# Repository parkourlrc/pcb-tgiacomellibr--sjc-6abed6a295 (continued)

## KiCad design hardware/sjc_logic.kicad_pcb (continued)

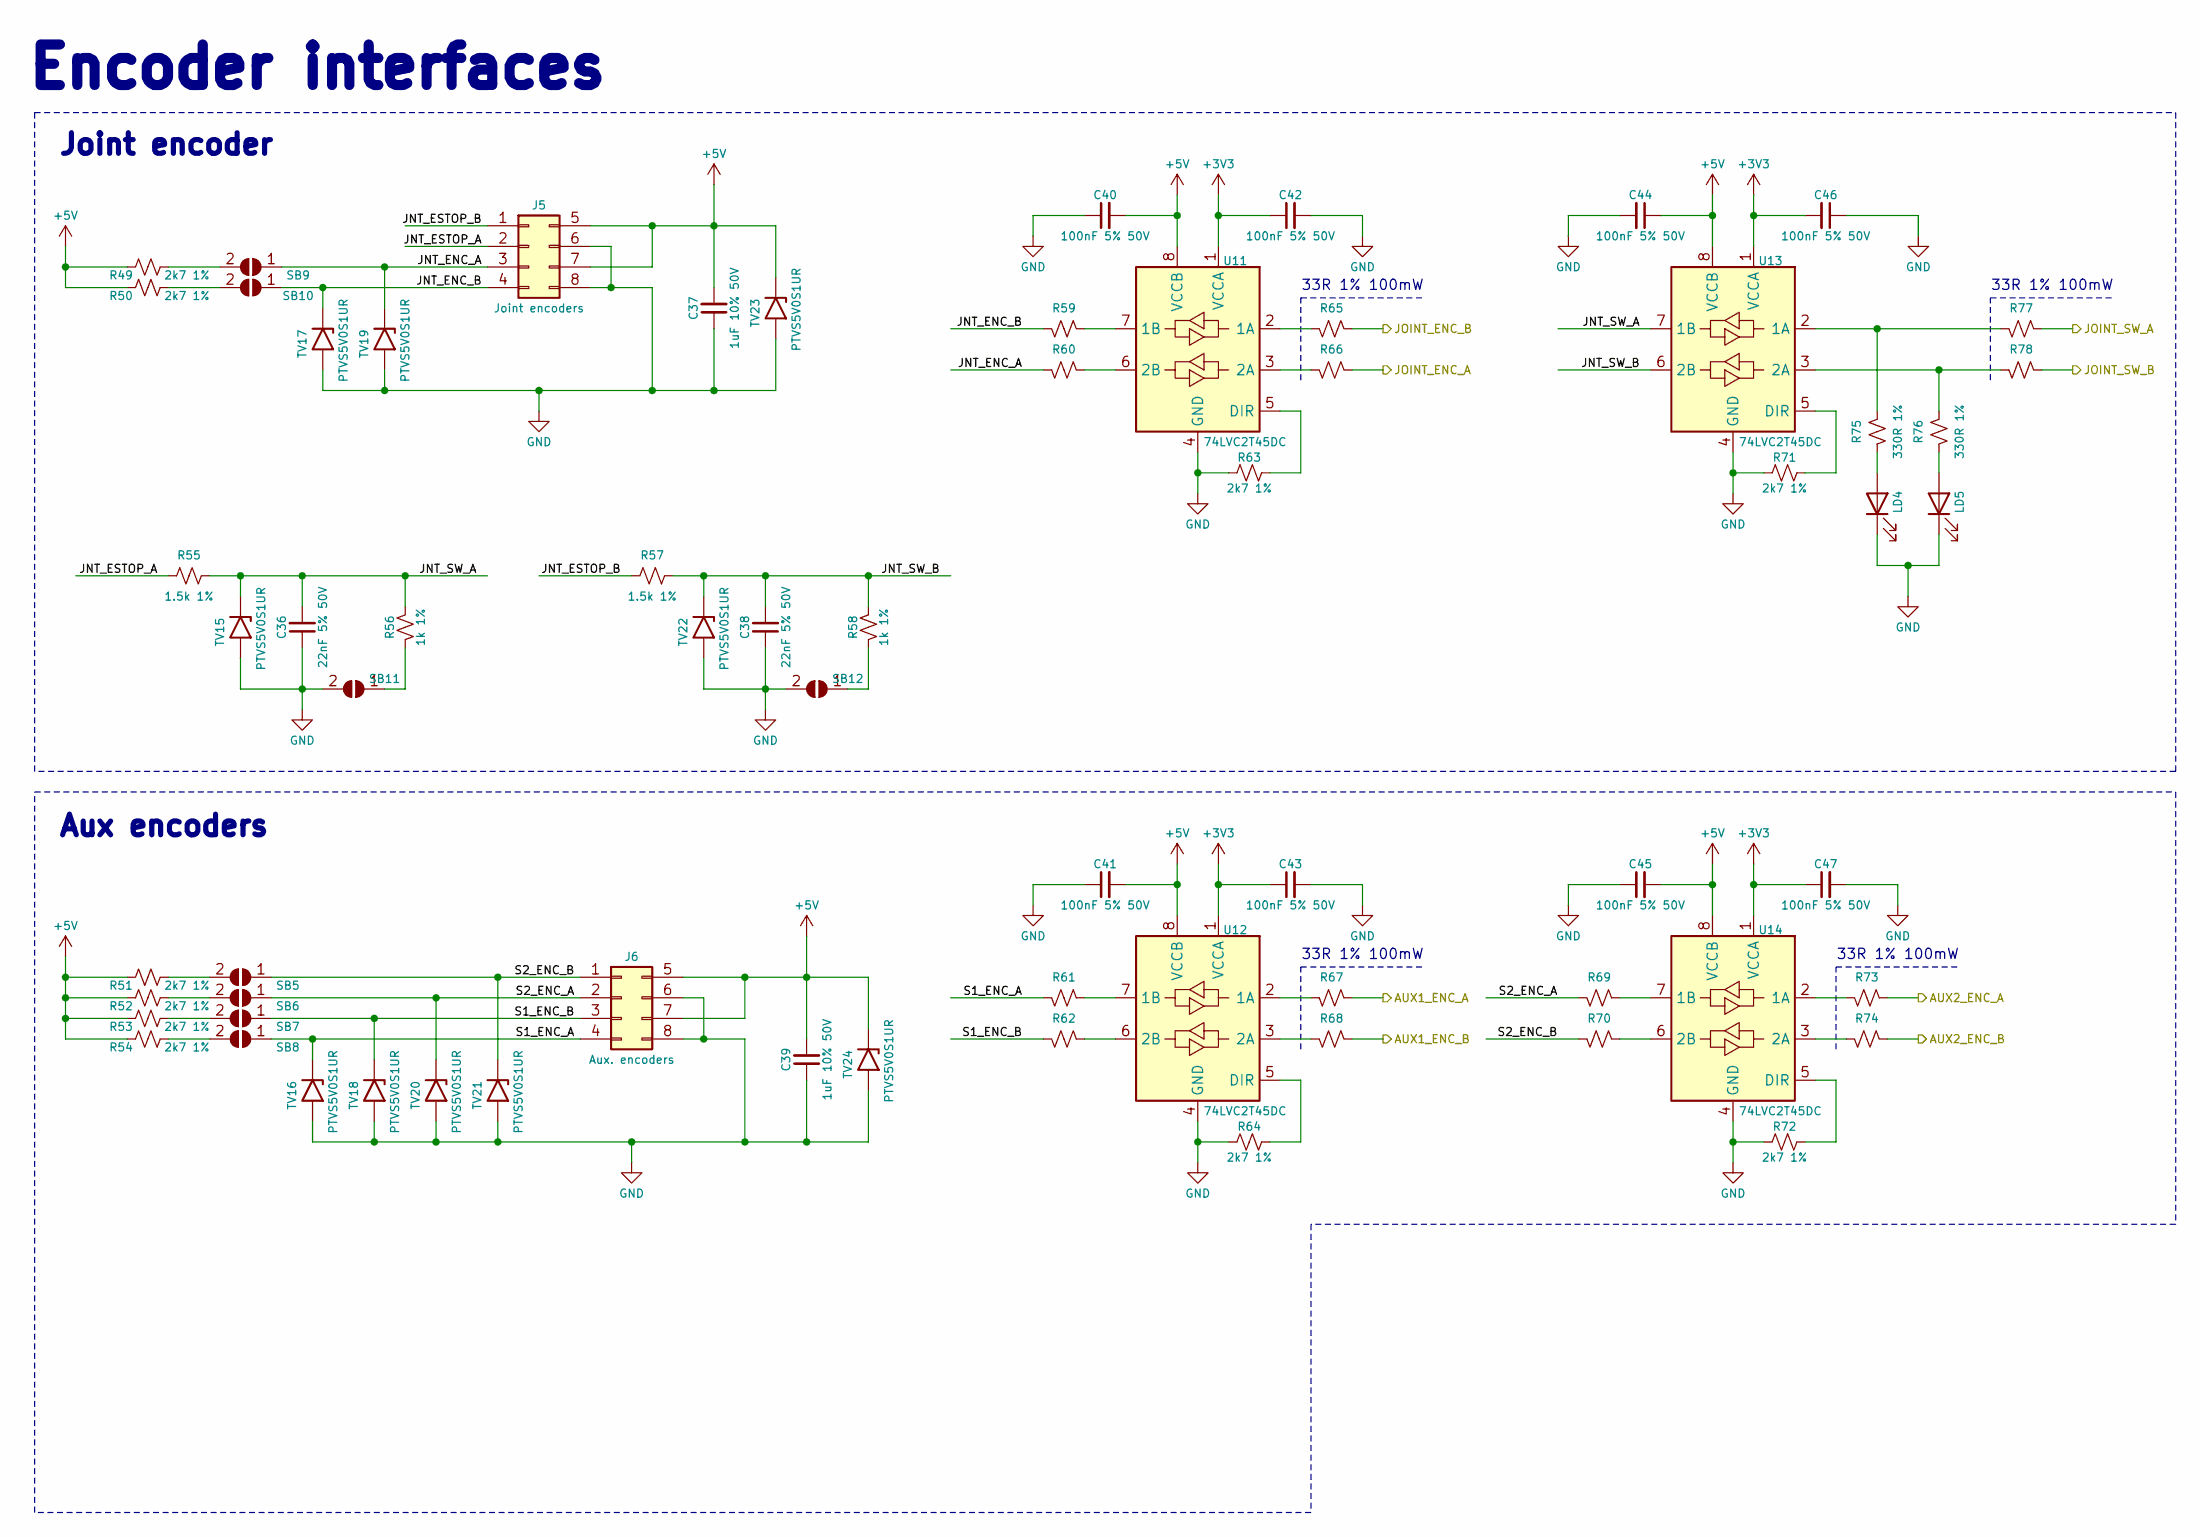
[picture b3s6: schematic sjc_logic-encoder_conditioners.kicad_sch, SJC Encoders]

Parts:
C36, C38: 22nF 5% 50V; C_0603_1608Metric; JLCPCB Part # C277528
C37, C39: 1uF 10% 50V; C_1206_3216Metric; JLCPCB Part # C1848
C40, C41, C42, C43, C44, C45, C46, C47: 100nF 5% 50V; C_0603_1608Metric; JLCPCB Part # C91183
J5: Joint encoders; Molex_Micro-Fit_3.0_43045-0812_2x04_P3.00mm_Vertical
J6: Aux. encoders; Molex_Micro-Fit_3.0_43045-0812_2x04_P3.00mm_Vertical
LD4, LD5: 1.8V @ 5mA; LED_0603_1608Metric_Pad1.05x0.95mm_HandSolder; JLCPCB Part # C165982
R49, R50, R51, R52, R53, R54, R63, R64, R71, R72: 2k7 1%; R_0603_1608Metric; JLCPCB Part # C114612
R55, R57: 1.5k 1%; R_0603_1608Metric; JLCPCB Part # C285210
R56, R58: 1k 1%; R_0603_1608Metric; JLCPCB Part # C22548
R59, R60, R61, R62, R65, R66, R67, R68, R69, R70, R73, R74, R77, R78: 33R 1%; R_0603_1608Metric; JLCPCB Part # C108661
R75, R76: 330R 1%; R_0603_1608Metric; JLCPCB Part # C144102
SB5, SB6, SB7, SB8, SB9, SB10, SB11, SB12: SolderJumper-2_P1.3mm_Open_RoundedPad1.0x1.5mm
TV15, TV16, TV17, TV18, TV19, TV20, TV21, TV22, TV23, TV24: PTVS5V0S1UR; D_SOD-123; JLCPCB Part # C478011
U11, U12, U13, U14: 74LVC2T45DC; VSSOP-8_2.3x2mm_P0.5mm; JLCPCB Part # C730237

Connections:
+3V3: C42.1, C43.1, C46.2, C47.1, U11.1 (VCCA), U12.1 (VCCA), U13.1 (VCCA), U14.1 (VCCA); also elsewhere on the board
+5V: C37.2, C39.2, C40.2, C41.2, C44.1, C45.2, J5.5, J5.7, J6.5, J6.7, R49.2, R50.2, R51.1, R52.1, R53.1, R54.1, TV23.1 (K), TV24.1 (K), U11.8 (VCCB), U12.8 (VCCB), U13.8 (VCCB), U14.8 (VCCB); also elsewhere on the board
/Control/AUX1_ENC_CH1: R67.1; also elsewhere on the board
/Control/AUX1_ENC_CH2: R68.1; also elsewhere on the board
/Control/AUX2_ENC_CH1: R73.1; also elsewhere on the board
/Control/AUX2_ENC_CH2: R74.1; also elsewhere on the board
/Control/JOINT_ENC_CH1: R66.1; also elsewhere on the board
/Control/JOINT_ENC_CH2: R65.1; also elsewhere on the board
/Control/JOINT_SW_L: R77.1; also elsewhere on the board
/Control/JOINT_SW_R: R78.1; also elsewhere on the board
/Encoder Conditioners/JNT_ENC_A: J5.3, R60.2, SB9.1 (A), TV19.1 (K)
/Encoder Conditioners/JNT_ENC_B: J5.4, R59.2, SB10.1 (A), TV17.1 (K)
/Encoder Conditioners/JNT_ESTOP_A: J5.2, R55.1
/Encoder Conditioners/JNT_ESTOP_B: J5.1, R57.1
/Encoder Conditioners/JNT_SW_A: C36.2, R55.2, R56.1, TV15.1 (K), U13.7 (1B)
/Encoder Conditioners/JNT_SW_B: C38.2, R57.2, R58.1, TV22.1 (K), U13.6 (2B)
/Encoder Conditioners/S1_ENC_A: J6.4, R61.2, SB8.1 (A), TV16.1 (K)
/Encoder Conditioners/S1_ENC_B: J6.3, R62.2, SB7.1 (A), TV18.1 (K)
/Encoder Conditioners/S2_ENC_A: J6.2, R69.2, SB6.1 (A), TV20.1 (K)
/Encoder Conditioners/S2_ENC_B: J6.1, R70.2, SB5.1 (A), TV21.1 (K)
GND: C36.1, C37.1, C38.1, C39.1, C40.1, C41.1, C42.2, C43.2, C44.2, C45.1, C46.1, C47.2, J5.6, J5.8, J6.6, J6.8, LD4.1 (K), LD5.1 (K), R63.1, R64.1, R71.1, R72.1, SB11.2 (B), SB12.2 (B), TV15.2 (A), TV16.2 (A), TV17.2 (A), TV18.2 (A), TV19.2 (A), TV20.2 (A), TV21.2 (A), TV22.2 (A), TV23.2 (A), TV24.2 (A), U11.4 (GND), U12.4 (GND), U13.4 (GND), U14.4 (GND); also elsewhere on the board
unnamed: LD4.2 (A), R75.2
unnamed: LD5.2 (A), R76.2
unnamed: R51.2, SB5.2 (B)
unnamed: R52.2, SB6.2 (B)
unnamed: R53.2, SB7.2 (B)
unnamed: R54.2, SB8.2 (B)
unnamed: R49.1, SB9.2 (B)
unnamed: R50.1, SB10.2 (B)
unnamed: R56.2, SB11.1 (A)
unnamed: R58.2, SB12.1 (A)
unnamed: R65.2, U11.2 (1A)
unnamed: R59.1, U11.7 (1B)
unnamed: R66.2, U11.3 (2A)
unnamed: R60.1, U11.6 (2B)
unnamed: R63.2, U11.5 (DIR)
unnamed: R67.2, U12.2 (1A)
unnamed: R61.1, U12.7 (1B)
unnamed: R68.2, U12.3 (2A)
unnamed: R62.1, U12.6 (2B)
unnamed: R64.2, U12.5 (DIR)
unnamed: R75.1, R77.2, U13.2 (1A)
unnamed: R76.1, R78.2, U13.3 (2A)
unnamed: R71.2, U13.5 (DIR)
unnamed: R73.2, U14.2 (1A)
unnamed: R69.1, U14.7 (1B)
unnamed: R74.2, U14.3 (2A)
unnamed: R70.1, U14.6 (2B)
unnamed: R72.2, U14.5 (DIR)

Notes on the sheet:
33R 1% 100mW
Joint encoder
Aux encoders
Encoder interfaces

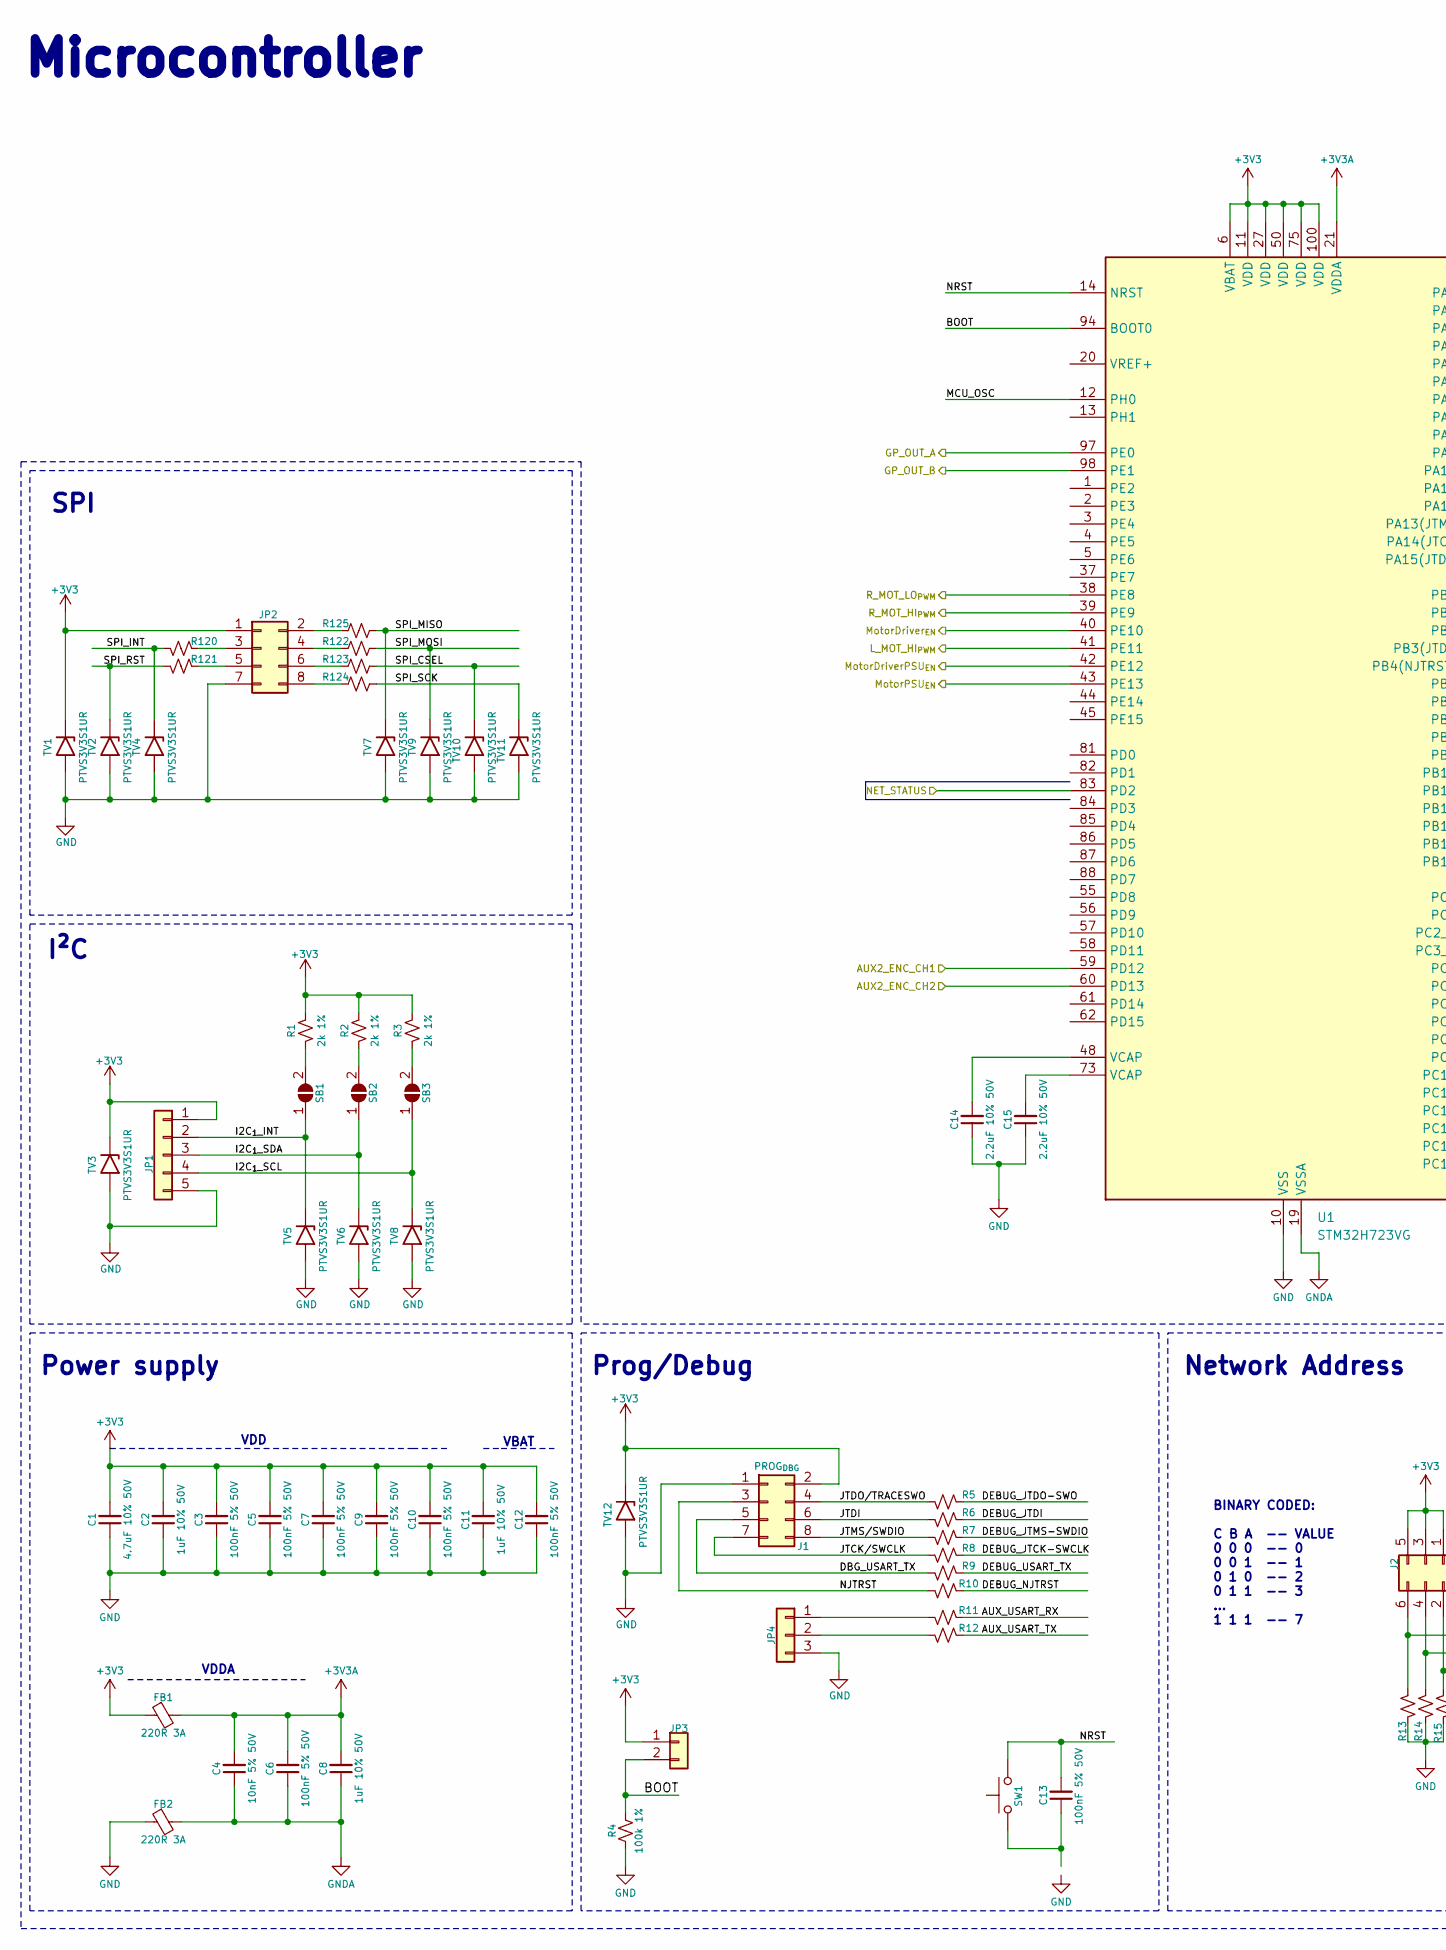
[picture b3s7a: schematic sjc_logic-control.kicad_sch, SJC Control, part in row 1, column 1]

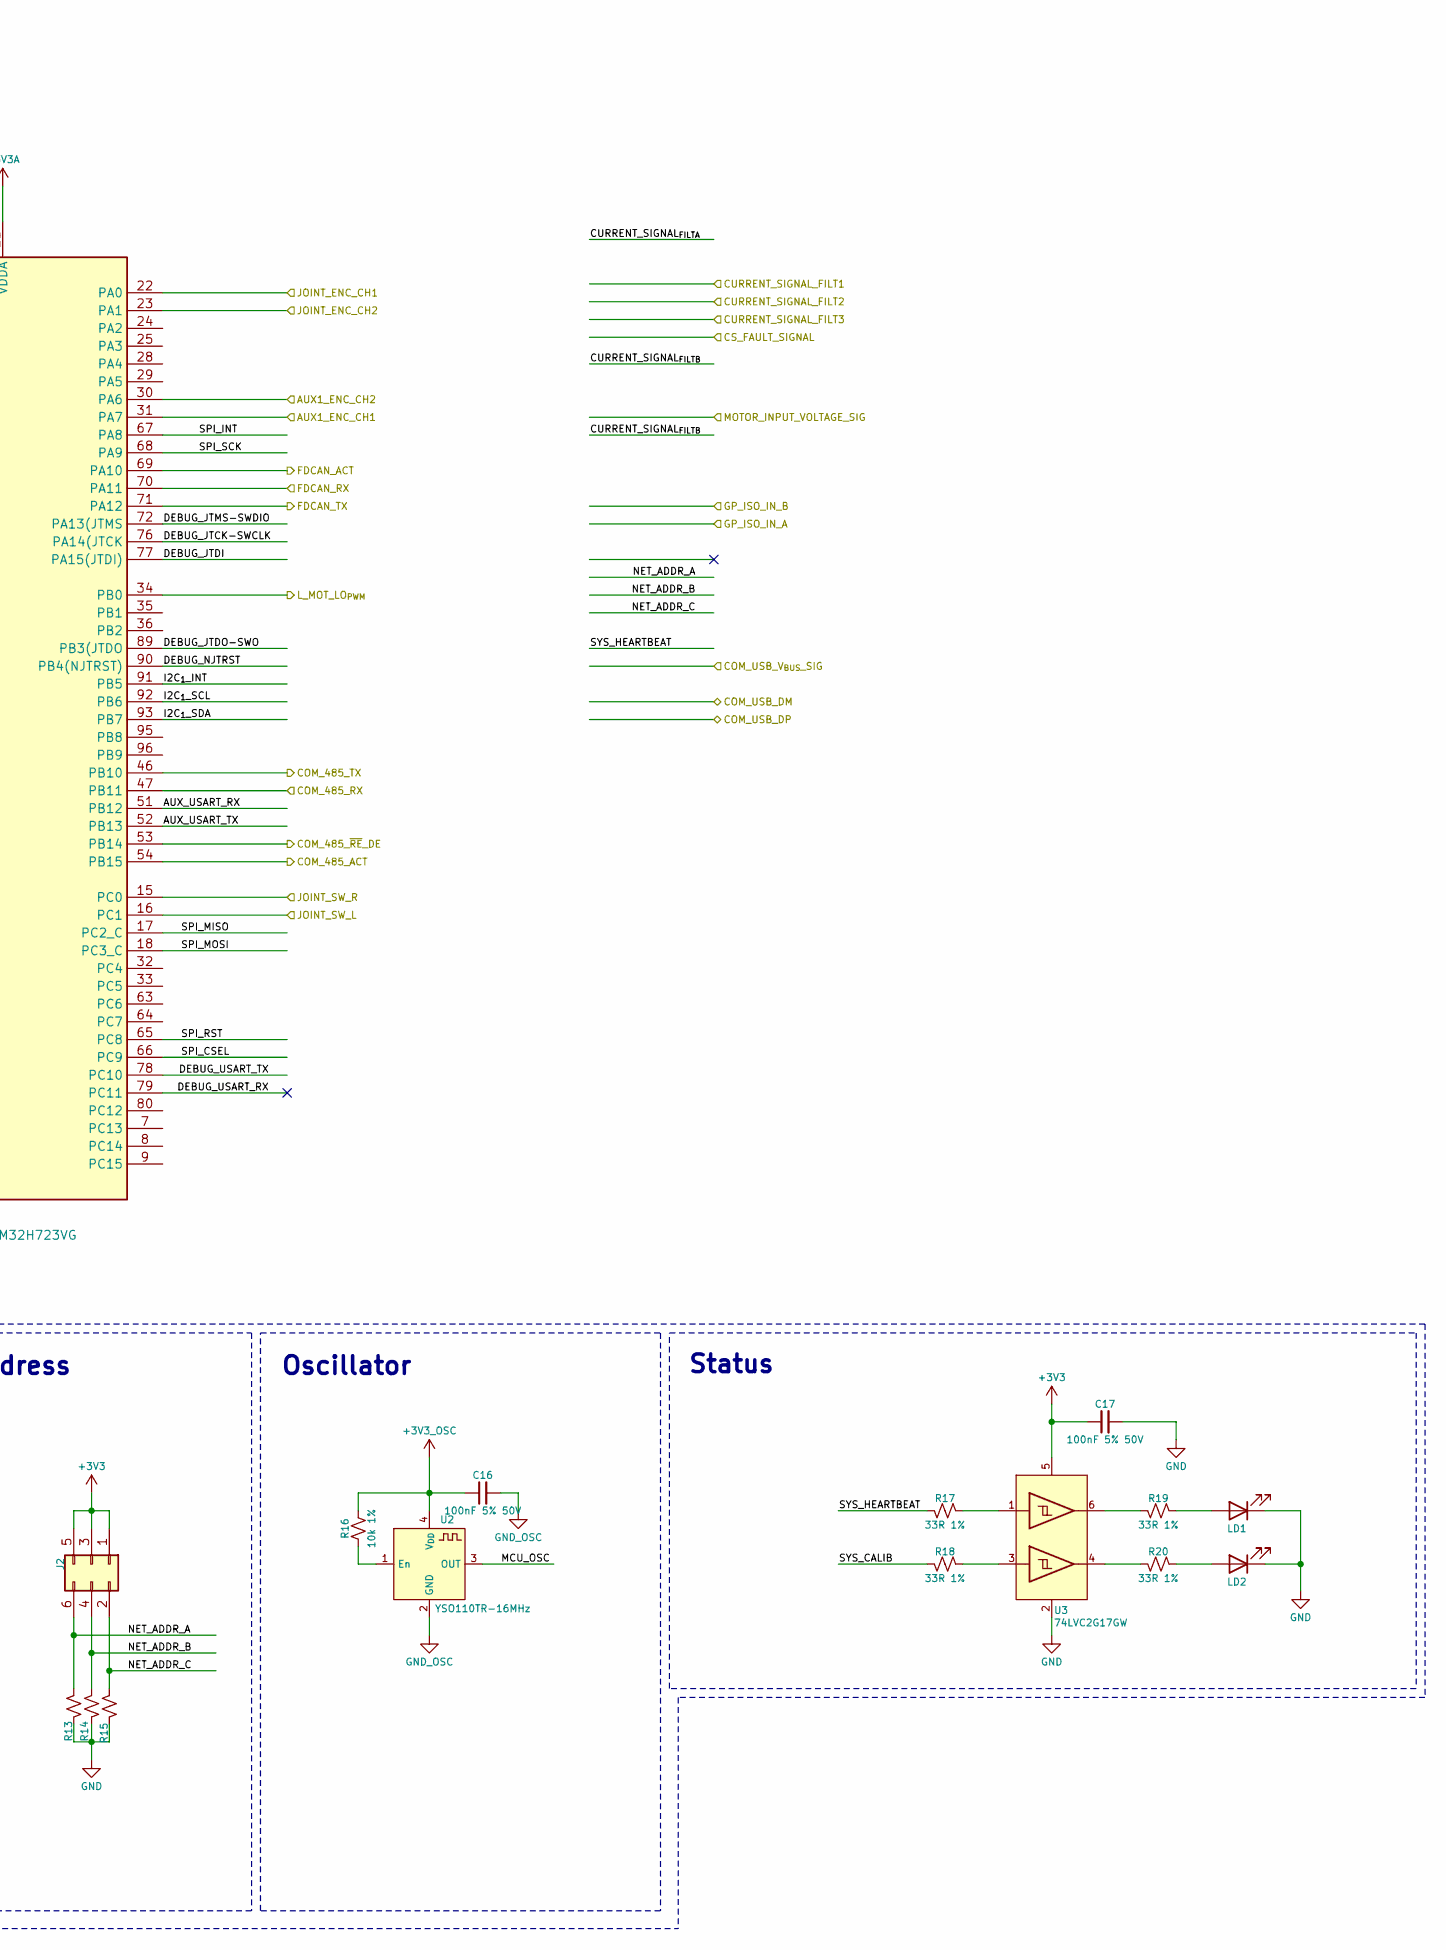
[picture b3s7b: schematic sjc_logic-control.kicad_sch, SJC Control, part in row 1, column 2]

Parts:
C1: 4.7uF 10% 50V; C_1206_3216Metric_Pad1.33x1.80mm_HandSolder; JLCPCB Part # C77096
C2, C8, C11: 1uF 10% 50V; C_1206_3216Metric; JLCPCB Part # C1848
C3, C5, C6, C7, C9, C10, C12, C13, C16, C17: 100nF 5% 50V; C_0603_1608Metric; JLCPCB Part # C91183
C4: 10nF 5% 50V; C_0603_1608Metric; JLCPCB Part # C389113
C14, C15: 2.2uF 10% 50V; C_1206_3216Metric; JLCPCB Part # C50254
FB1, FB2: 220R 3A; L_0805_2012Metric_Pad1.05x1.20mm_HandSolder; JLCPCB Part # C76818
J1: PROG_{DBG}; PinHeader_2x04_P2.54mm_Vertical; JLCPCB Part # C225519
J2: NET ADDRESS; PinHeader_2x03_P2.54mm_Vertical; JLCPCB Part # C225518
JP1: I2C; PinHeader_1x05_P2.54mm_Vertical; JLCPCB Part # C225477
JP2: I2C; PinHeader_2x04_P2.54mm_Vertical; JLCPCB Part # C225477
JP3: Boot; PinHeader_1x02_P2.54mm_Vertical; JLCPCB Part # C225477
JP4: Aux Usart; PinHeader_1x03_P2.54mm_Vertical; JLCPCB Part # C225477
LD1, LD2: 1.8V @ 5mA; LED_0603_1608Metric_Pad1.05x0.95mm_HandSolder; JLCPCB Part # C165982
R1, R2, R3: 2k 1%; R_0603_1608Metric; JLCPCB Part # C105576
R4: 100k 1%; R_0603_1608Metric; JLCPCB Part # C14675
R5, R6, R7, R8, R9, R10, R11, R12, R17, R18, R19, R20, R120, R121, R122, R123, R124, R125: 33R 1%; R_0603_1608Metric; JLCPCB Part # C108661
R13, R14, R15, R16: 10k 1%; R_0603_1608Metric; JLCPCB Part # C98220
SB1, SB2, SB3: SolderJumper-2_P1.3mm_Open_RoundedPad1.0x1.5mm
SW1: Tactile Switch; SW_Tactile_SPST_NO_Straight_CK_PTS636Sx25SMTRLFS; JLCPCB Part # C2689642
TV1, TV2, TV3, TV4, TV5, TV6, TV7, TV8, TV9, TV10, TV11, TV12: PTVS3V3S1UR; D_SOD-123; JLCPCB Part # C183521
U1: STM32H723VG; LQFP-100_14x14mm_P0.5mm; JLCPCB Part # C730142
U2: YSO110TR-16MHz; Oscillator_SMD_YXC_YSO110TR_7050-4Pin_7.0x5.0mm; JLCPCB Part # C669093
U3: 74LVC2G17GW; SOT-363_SC-70-6; JLCPCB Part # C80500

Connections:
+3V3: C1.2, C2.2, C3.2, C5.2, C7.2, C9.2, C10.2, C11.2, C12.2, C17.1, FB1.1, J1.2, J2.1, J2.3, J2.5, JP1.1, JP2.1, JP3.1, R1.2, R2.2, R3.2, TV1.1 (K), TV3.1 (K), TV12.1 (K), U1.6 (VBAT), U1.11 (VDD), U1.27 (VDD), U1.50 (VDD), U1.75 (VDD), U1.100 (VDD), U3.5 (VCC); also elsewhere on the board
+3V3A: C4.2, C6.2, C8.2, FB1.2, U1.21 (VDDA)
+3V3_OSC: C16.1, R16.2, U2.4 (V_{DD}); also elsewhere on the board
/Communication Interfaces/CAN_ACT: U1.69 (PA10); also elsewhere on the board
/Communication Interfaces/CAN_RX: U1.70 (PA11); also elsewhere on the board
/Communication Interfaces/CAN_TX: U1.71 (PA12); also elsewhere on the board
/Communication Interfaces/NET_STATUS: U1.83 (PD2); also elsewhere on the board
/Communication Interfaces/RS485_ACT: U1.54 (PB15); also elsewhere on the board
/Communication Interfaces/RS485_RX: U1.47 (PB11); also elsewhere on the board
/Communication Interfaces/RS485_TX: U1.46 (PB10); also elsewhere on the board
/Communication Interfaces/RS485_~RE_DE: U1.53 (PB14); also elsewhere on the board
/Control/AUX1_ENC_CH1: U1.31 (PA7); also elsewhere on the board
/Control/AUX1_ENC_CH2: U1.30 (PA6); also elsewhere on the board
/Control/AUX2_ENC_CH1: U1.59 (PD12); also elsewhere on the board
/Control/AUX2_ENC_CH2: U1.60 (PD13); also elsewhere on the board
/Control/AUX_USART_RX: R11.1, U1.51 (PB12)
/Control/AUX_USART_TX: R12.1, U1.52 (PB13)
/Control/BOOT: JP3.2, R4.2, U1.94 (BOOT0)
/Control/DBG_USART_TX: J1.5, R9.2
/Control/DEBUG_JTCK-SWCLK: R8.1, U1.76 (PA14(JTCK)
/Control/DEBUG_JTDI: R6.1, U1.77 (PA15(JTDI))
/Control/DEBUG_JTDO-SWO: R5.1, U1.89 (PB3(JTDO)
/Control/DEBUG_JTMS-SWDIO: R7.1, U1.72 (PA13(JTMS)
/Control/DEBUG_NJTRST: R10.1, U1.90 (PB4(NJTRST))
/Control/DEBUG_USART_RX: U1.79 (PC11)
/Control/DEBUG_USART_TX: R9.1, U1.78 (PC10)
/Control/GP_OUT_A: U1.97 (PE0); also elsewhere on the board
/Control/GP_OUT_B: U1.98 (PE1); also elsewhere on the board
/Control/I2C_{1}_INT: JP1.2, SB1.1 (A), TV5.1 (K), U1.91 (PB5)
/Control/I2C_{1}_SCL: JP1.4, SB3.1 (A), TV8.1 (K), U1.92 (PB6)
/Control/I2C_{1}_SDA: JP1.3, SB2.1 (A), TV6.1 (K), U1.93 (PB7)
/Control/JOINT_ENC_CH1: U1.22 (PA0); also elsewhere on the board
/Control/JOINT_ENC_CH2: U1.23 (PA1); also elsewhere on the board
/Control/JOINT_SW_L: U1.16 (PC1); also elsewhere on the board
/Control/JOINT_SW_R: U1.15 (PC0); also elsewhere on the board
/Control/JTCK/SWCLK: J1.7, R8.2
/Control/JTDI: J1.6, R6.2
/Control/JTDO/TRACESWO: J1.4, R5.2
/Control/JTMS/SWDIO: J1.8, R7.2
/Control/L_MOT_HI_{PWM}: U1.41 (PE11); also elsewhere on the board
/Control/L_MOT_LO_{PWM}: U1.34 (PB0); also elsewhere on the board
/Control/MCU_OSC: U1.12 (PH0), U2.3 (OUT)
/Control/MotorDriverPSU_{EN}: U1.42 (PE12); also elsewhere on the board
/Control/MotorDriver_{EN}: U1.40 (PE10); also elsewhere on the board
/Control/MotorPSU_{EN}: U1.43 (PE13); also elsewhere on the board
/Control/NET_ADDR_A: J2.6, R13.1
/Control/NET_ADDR_B: J2.4, R14.1
/Control/NET_ADDR_C: J2.2, R15.1
/Control/NJTRST: J1.3, R10.2
/Control/NRST: C13.2, SW1.2, U1.14 (NRST)
/Control/R_MOT_HI_{PWM}: U1.39 (PE9); also elsewhere on the board
/Control/R_MOT_LO_{PWM}: U1.38 (PE8); also elsewhere on the board
/Control/SPI_CSEL: R123.2, TV10.1 (K), U1.66 (PC9)
/Control/SPI_INT: R120.2, TV4.1 (K), U1.67 (PA8)
/Control/SPI_MISO: R125.2, TV7.1 (K), U1.17 (PC2_C)
/Control/SPI_MOSI: R122.2, TV9.1 (K), U1.18 (PC3_C)
/Control/SPI_RST: R121.2, TV2.1 (K), U1.65 (PC8)
/Control/SPI_SCK: R124.2, TV11.1 (K), U1.68 (PA9)
/Control/SYS_CALIB: R18.2
/Control/SYS_HEARTBEAT: R17.2
GND: C1.1, C2.1, C3.1, C5.1, C7.1, C9.1, C10.1, C11.1, C12.1, C14.1, C15.1, C17.2, FB2.1, J1.1, JP1.5, JP2.7, JP4.3, LD1.1 (K), LD2.1 (K), R4.1, R13.2, R14.2, R15.2, TV1.2 (A), TV2.2 (A), TV3.2 (A), TV4.2 (A), TV5.2 (A), TV6.2 (A), TV7.2 (A), TV8.2 (A), TV9.2 (A), TV10.2 (A), TV11.2 (A), TV12.2 (A), U1.10 (VSS), U1.26 (VSS), U1.49 (VSS), U1.74 (VSS), U1.99 (VSS), U3.2 (GND); also elsewhere on the board
GNDA: C4.1, C6.1, C8.1, FB2.2, U1.19 (VSSA)
GND_OSC: C16.2, U2.2 (GND); also elsewhere on the board
unnamed: C13.1, SW1.1
unnamed: C14.2, U1.48 (VCAP)
unnamed: C15.2, U1.73 (VCAP)
unnamed: JP2.2, R125.1
unnamed: JP2.3, R120.1
unnamed: JP2.4, R122.1
unnamed: JP2.5, R121.1
unnamed: JP2.6, R123.1
unnamed: JP2.8, R124.1
unnamed: JP4.1, R11.2
unnamed: JP4.2, R12.2
unnamed: LD1.2 (A), R19.1
unnamed: LD2.2 (A), R20.1
unnamed: R1.1, SB1.2 (B)
unnamed: R2.1, SB2.2 (B)
unnamed: R3.1, SB3.2 (B)
unnamed: R16.1, U2.1 (En)
unnamed: R17.1, U3.1 (1A)
unnamed: R19.2, U3.6 (1Y)
unnamed: R18.1, U3.3 (2A)
unnamed: R20.2, U3.4 (2Y)

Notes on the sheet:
Microcontroller
VBAT
Status
SPI
Network Address
BINARY CODED: C B A -- VALUE 0 0 0 -- 0 0 0 1 -- 1 0 1 0 -- 2 0 1 1 -- 3 ... 1 1 1 -- 7
Prog/Debug
Power supply
Oscillator
I²C
VDDA
VDD

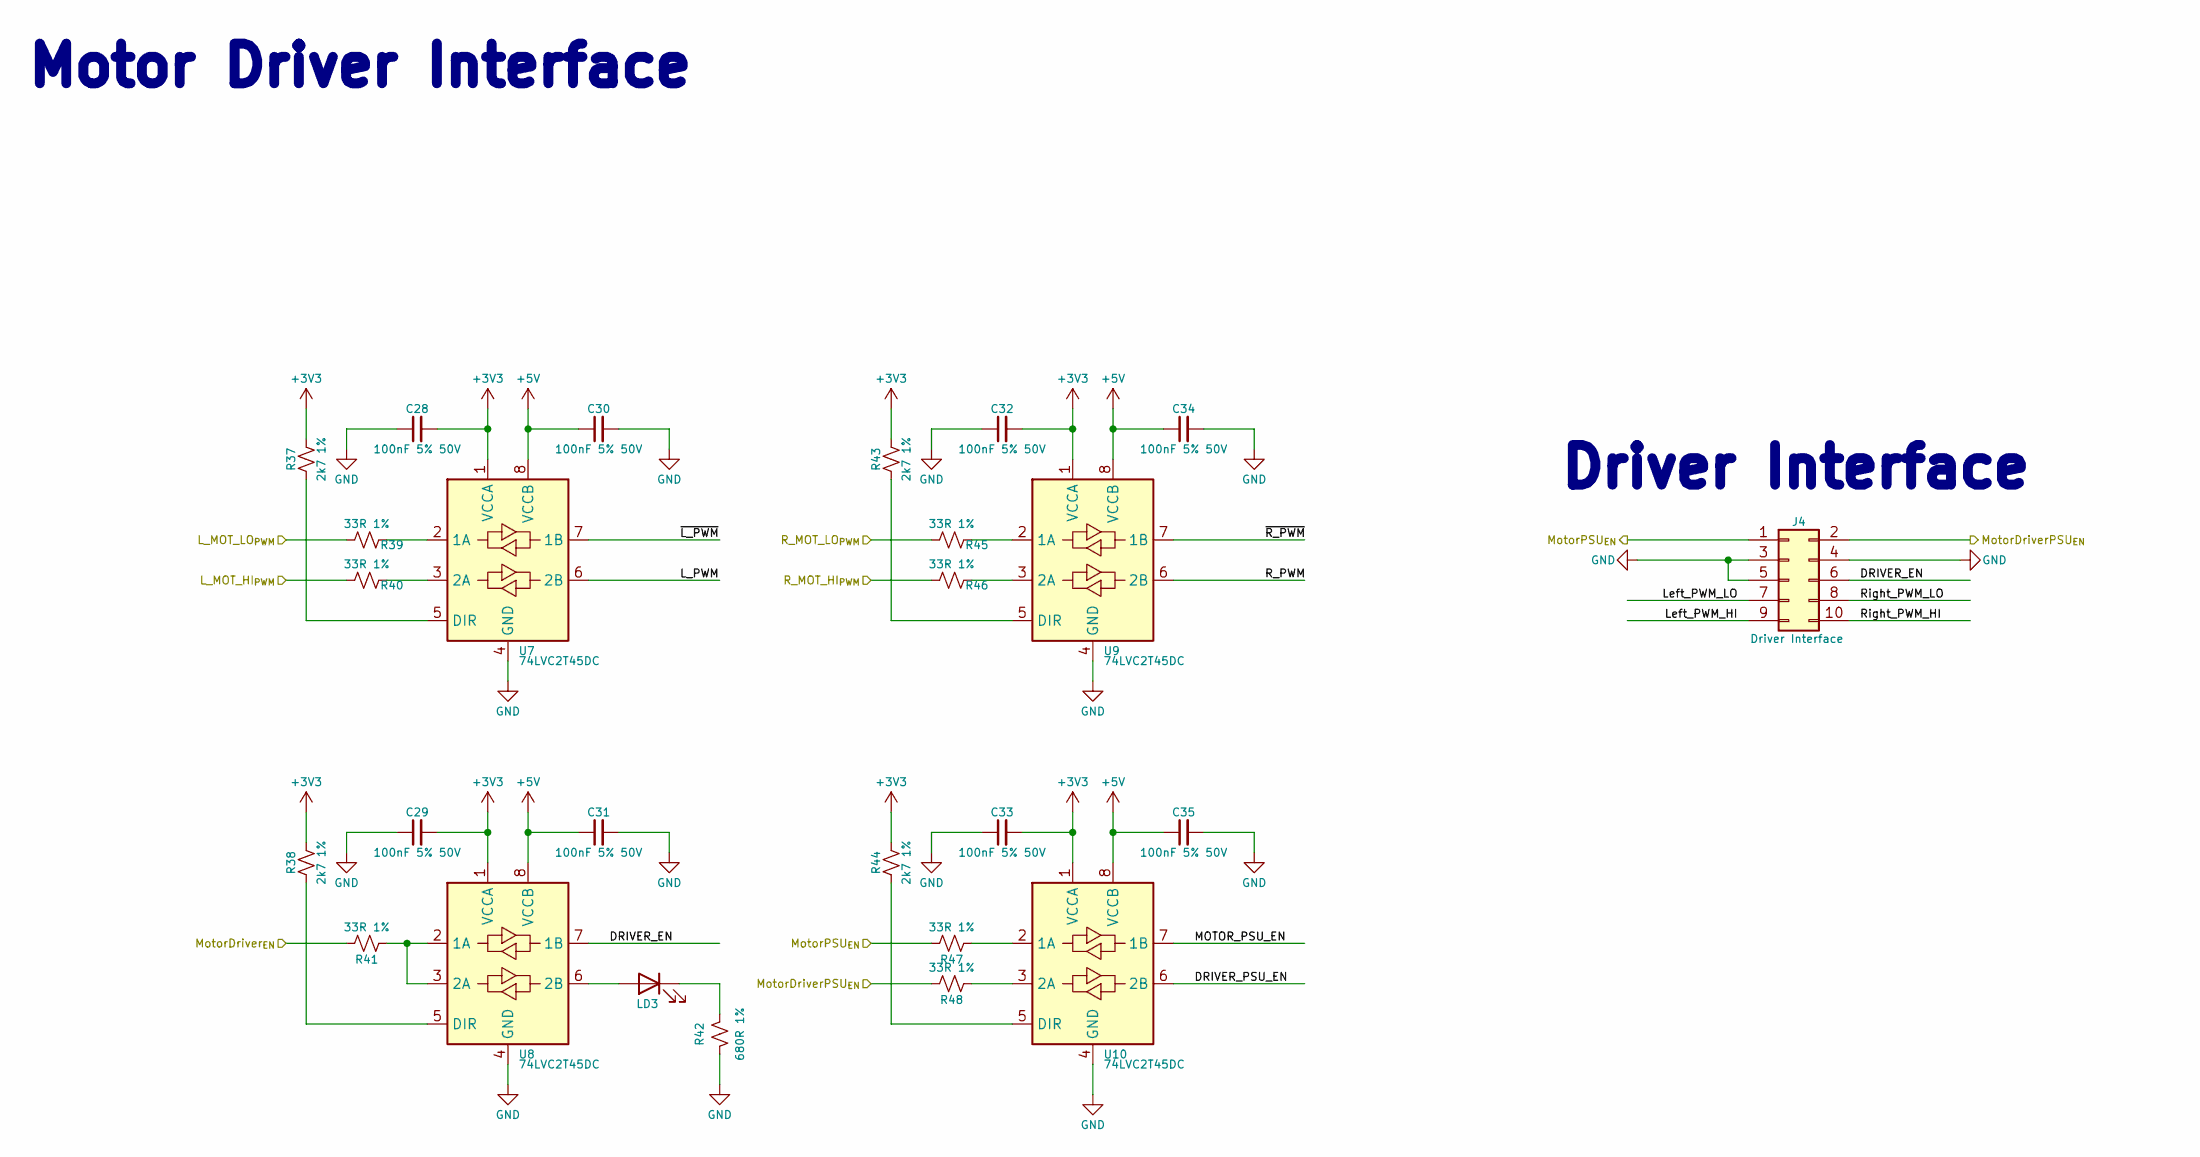
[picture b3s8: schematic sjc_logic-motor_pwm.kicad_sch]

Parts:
C28, C29, C30, C31, C32, C33, C34, C35: 100nF 5% 50V; C_0603_1608Metric; JLCPCB Part # C91183
J4: Driver Interface; PinHeader_2x05_P2.54mm_Vertical; JLCPCB Part # C225520
LD3: 1.8V @ 5mA; LED_0603_1608Metric_Pad1.05x0.95mm_HandSolder; JLCPCB Part # C165982
R37, R38, R43, R44: 2k7 1%; R_0603_1608Metric; JLCPCB Part # C114612
R39, R40, R41, R45, R46, R47, R48: 33R 1%; R_0603_1608Metric; JLCPCB Part # C108661
R42: 680R 1%; R_0603_1608Metric; JLCPCB Part # C966615
U7, U8, U9, U10: 74LVC2T45DC; VSSOP-8_2.3x2mm_P0.5mm; JLCPCB Part # C730237

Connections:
+3V3: C28.2, C29.2, C32.2, C33.2, R37.2, R38.2, R43.2, R44.2, U7.1 (VCCA), U8.1 (VCCA), U9.1 (VCCA), U10.1 (VCCA); also elsewhere on the board
+5V: C30.1, C31.1, C34.1, C35.1, U7.8 (VCCB), U8.8 (VCCB), U9.8 (VCCB), U10.8 (VCCB); also elsewhere on the board
/Control/L_MOT_HI_{PWM}: R40.2; also elsewhere on the board
/Control/L_MOT_LO_{PWM}: R39.2; also elsewhere on the board
/Control/MotorDriverPSU_{EN}: J4.2, R48.2; also elsewhere on the board
/Control/MotorDriver_{EN}: R41.2; also elsewhere on the board
/Control/MotorPSU_{EN}: J4.1, R47.2; also elsewhere on the board
/Control/R_MOT_HI_{PWM}: R46.2; also elsewhere on the board
/Control/R_MOT_LO_{PWM}: R45.2; also elsewhere on the board
/Motor PWM/DRIVER_EN: J4.6, U8.7 (1B)
/Motor PWM/DRIVER_PSU_EN: U10.6 (2B)
/Motor PWM/L_PWM: U7.6 (2B)
/Motor PWM/Left_PWM_HI: J4.9
/Motor PWM/Left_PWM_LO: J4.7
/Motor PWM/MOTOR_PSU_EN: U10.7 (1B)
/Motor PWM/R_PWM: U9.6 (2B)
/Motor PWM/Right_PWM_HI: J4.10
/Motor PWM/Right_PWM_LO: J4.8
/Motor PWM/~L_PWM: U7.7 (1B)
/Motor PWM/~R_PWM: U9.7 (1B)
GND: C28.1, C29.1, C30.2, C31.2, C32.1, C33.1, C34.2, C35.2, J4.3, J4.4, J4.5, R42.2, U7.4 (GND), U8.4 (GND), U9.4 (GND), U10.4 (GND); also elsewhere on the board
unnamed: LD3.2 (A), U8.6 (2B)
unnamed: LD3.1 (K), R42.1
unnamed: R39.1, U7.2 (1A)
unnamed: R40.1, U7.3 (2A)
unnamed: R37.1, U7.5 (DIR)
unnamed: R41.1, U8.2 (1A), U8.3 (2A)
unnamed: R38.1, U8.5 (DIR)
unnamed: R45.1, U9.2 (1A)
unnamed: R46.1, U9.3 (2A)
unnamed: R43.1, U9.5 (DIR)
unnamed: R47.1, U10.2 (1A)
unnamed: R48.1, U10.3 (2A)
unnamed: R44.1, U10.5 (DIR)

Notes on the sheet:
Driver Interface
Motor Driver Interface

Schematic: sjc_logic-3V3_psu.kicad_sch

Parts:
C79: 22uF 10% 25V; C_1206_3216Metric; JLCPCB Part # C2178233
C80, C81: 10uF 10% 50V; C_1206_3216Metric; JLCPCB Part # C13585
C82: 1uF 10% 50V; C_1206_3216Metric; JLCPCB Part # C1848
C83: 100nF 5% 50V; C_0603_1608Metric; JLCPCB Part # C91183
F4: 13.2V 500mA; Fuse_1206_3216Metric_Pad1.42x1.75mm_HandSolder; JLCPCB Part # C75464
LD15: 1.8V @ 5mA; LED_0603_1608Metric_Pad1.05x0.95mm_HandSolder; JLCPCB Part # C165982
R119: 330R 1%; R_0603_1608Metric; JLCPCB Part # C144102
TV33: PTVS3V3S1UR; D_SOD-123; JLCPCB Part # C183521
U27: NCP1117DT33; TO-252-2; JLCPCB Part # C88234

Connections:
+3V3: C81.2, C82.2, C83.2, F4.1, LD15.2 (A), TV33.1 (K); also elsewhere on the board
LOGIC_PSU_GND_FILT: C79.1, C80.1, C81.1, C82.1, C83.1, R119.2, TV33.2 (A), U27.1 (GND); also elsewhere on the board
LOGIC_PSU_VIN_FILT: C79.2, C80.2, U27.3 (VI); also elsewhere on the board
unnamed: LD15.1 (K), R119.1
unnamed: F4.2, U27.2 (VO)

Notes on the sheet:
3V3 Power Supply

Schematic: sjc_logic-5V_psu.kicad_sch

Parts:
C74: 22uF 10% 25V; C_1206_3216Metric; JLCPCB Part # C2178233
C75, C76: 10uF 10% 50V; C_1206_3216Metric; JLCPCB Part # C13585
C77: 1uF 10% 50V; C_1206_3216Metric; JLCPCB Part # C1848
C78: 100nF 5% 50V; C_0603_1608Metric; JLCPCB Part # C91183
F3: 13.2V 500mA; Fuse_1206_3216Metric_Pad1.42x1.75mm_HandSolder; JLCPCB Part # C75464
LD14: 1.8V @ 5mA; LED_0603_1608Metric_Pad1.05x0.95mm_HandSolder; JLCPCB Part # C165982
R118: 680R 1%; R_0603_1608Metric; JLCPCB Part # C966615
TV32: PTVS5V0S1UR; D_SOD-123; JLCPCB Part # C478011
U26: NCP1117DT50; TO-252-2; JLCPCB Part # C152470

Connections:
+5V: C76.2, C77.2, C78.2, F3.1, LD14.2 (A), TV32.1 (K); also elsewhere on the board
LOGIC_PSU_GND_FILT: C74.1, C75.1, C76.1, C77.1, C78.1, R118.2, TV32.2 (A), U26.1 (GND); also elsewhere on the board
LOGIC_PSU_VIN_FILT: C74.2, C75.2, U26.3 (VI); also elsewhere on the board
unnamed: LD14.1 (K), R118.1
unnamed: F3.2, U26.2 (VO)

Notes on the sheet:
5V Power Supply

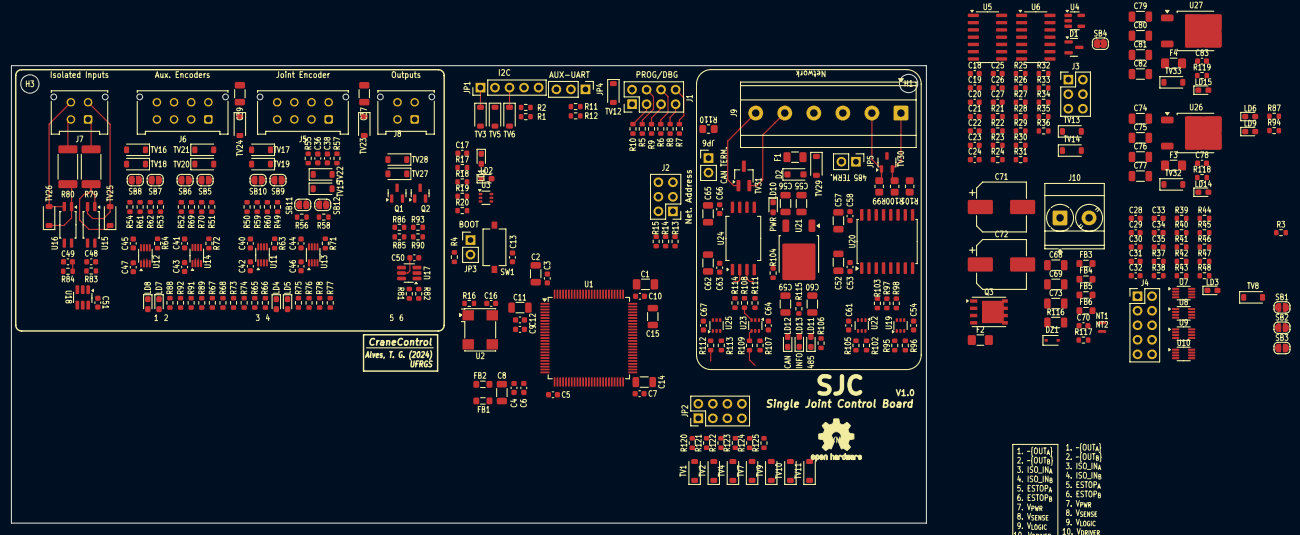
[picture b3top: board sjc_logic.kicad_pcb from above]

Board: 4 copper layers, 160.0 x 80.0 mm, 335 parts (0 on the bottom side), 228 nets.
